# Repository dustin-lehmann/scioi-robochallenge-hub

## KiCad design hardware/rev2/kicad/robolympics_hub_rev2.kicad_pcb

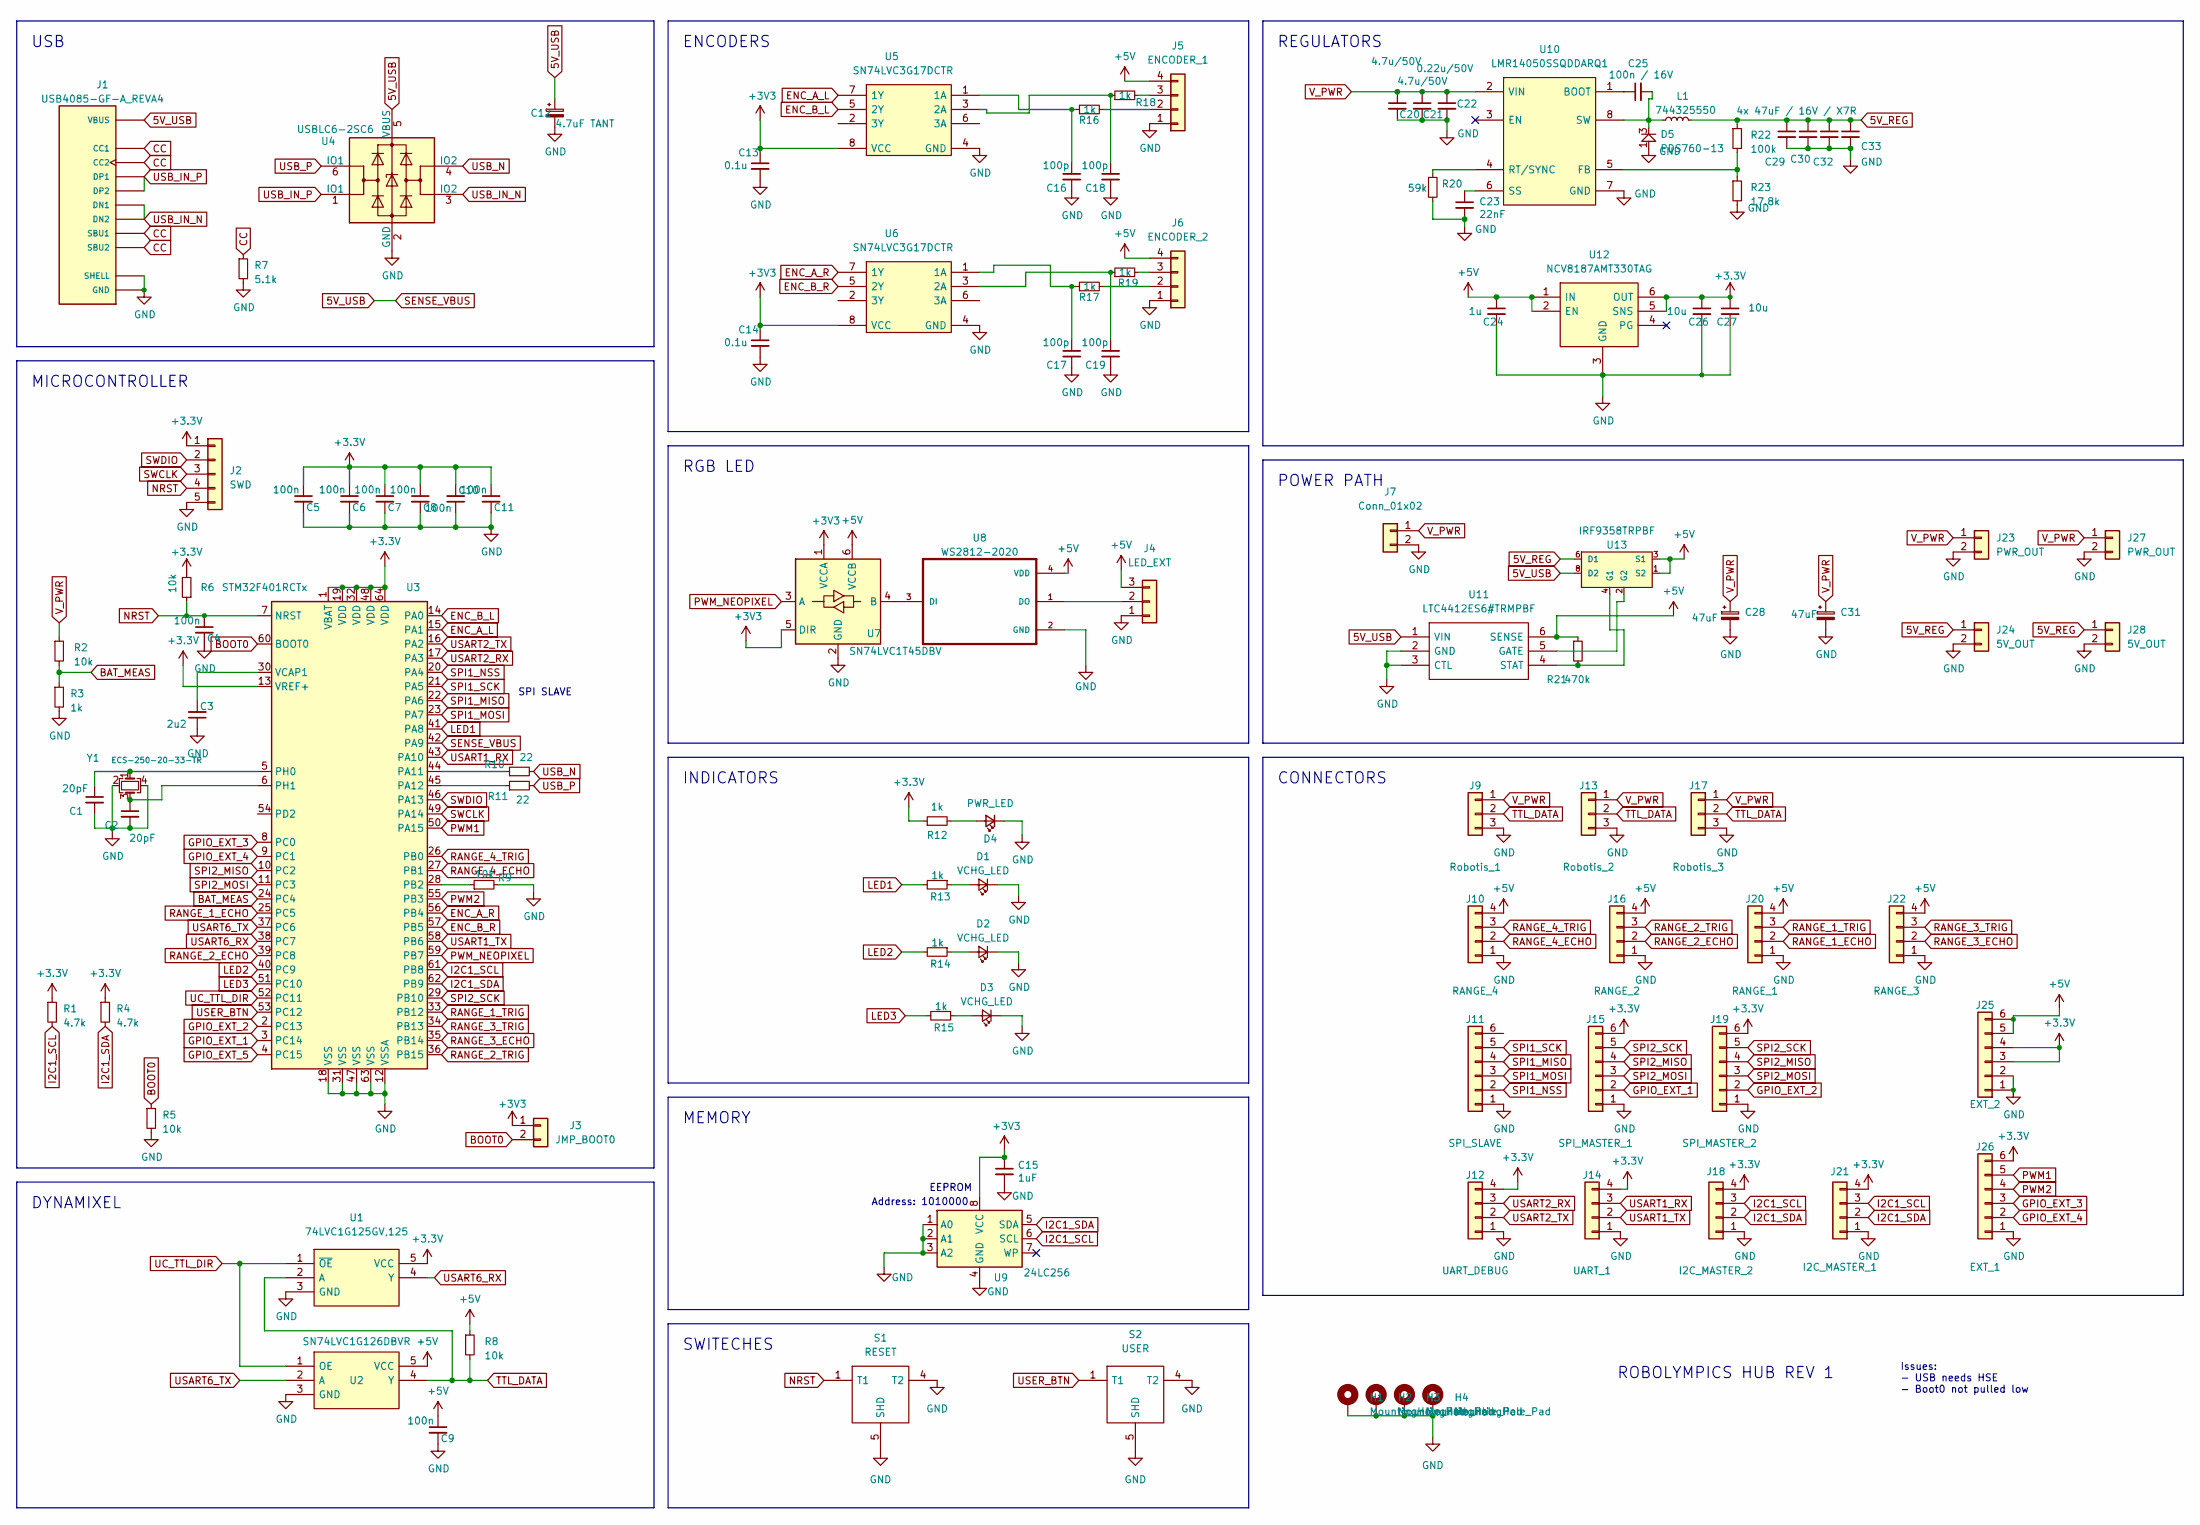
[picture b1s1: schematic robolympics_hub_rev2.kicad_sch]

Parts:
C1, C2: 20pF; C_0603_1608Metric
C3: 2u2; C_0805_2012Metric
C4, C5, C6, C7, C8, C9, C10, C11: 100n; C_0603_1608Metric
C12: 4.7uF TANT; C_1206_3216Metric
C13, C14: 0.1u; C_0603_1608Metric
C15: 1uF; C_0805_2012Metric
C16, C17, C18, C19: 100p; C_0603_1608Metric
C20, C21: 4.7u/50V; C_1210_3225Metric
C22: 0.22u/50V; C_0805_2012Metric
C23: 22nF; C_0603_1608Metric
C24: 1u; C_0805_2012Metric
C25: 100n / 16V; C_0603_1608Metric
C26, C27: 10u; C_0805_2012Metric
C28, C31: 47uF; CP_Elec_6.3x5.2
C29: 4x 47uF / 16V / X7R; C_1210_3225Metric
C30, C32, C33: C_Small; C_1210_3225Metric
D1, D2, D3: VCHG_LED; LED_0402_1005Metric
D4: PWR_LED; LED_0603_1608Metric
D5: PDS760-13; POWERDI5; Mouser Part Number 621-PDS760-F
H1, H2, H3, H4: MountingHole_Pad; MountingHole_2.7mm_M2.5_Pad
J1: USB4085-GF-A_REVA4; GCT_USB4085-GF-A_REVA4; PARTREV A4
J2: SWD; PinHeader_1x05_P2.54mm_Vertical
J3: JMP_BOOT0; PinHeader_1x02_P2.54mm_Vertical
J4: LED_EXT; Molex_KK-254_AE-6410-03A_1x03_P2.54mm_Vertical
J5: ENCODER_1; Molex_KK-254_AE-6410-04A_1x04_P2.54mm_Vertical
J6: ENCODER_2; Molex_KK-254_AE-6410-04A_1x04_P2.54mm_Vertical
J7: Conn_01x02; 691322310002
J9: Robotis_1; JST_EH_B3B-EH-A_1x03_P2.50mm_Vertical
J10: RANGE_4; Molex_KK-254_AE-6410-04A_1x04_P2.54mm_Vertical
J11: SPI_SLAVE; Molex_KK-254_AE-6410-06A_1x06_P2.54mm_Vertical
J12: UART_DEBUG; Molex_KK-254_AE-6410-04A_1x04_P2.54mm_Vertical
J13: Robotis_2; JST_EH_B3B-EH-A_1x03_P2.50mm_Vertical
J14: UART_1; Molex_KK-254_AE-6410-04A_1x04_P2.54mm_Vertical
J15: SPI_MASTER_1; Molex_KK-254_AE-6410-06A_1x06_P2.54mm_Vertical
J16: RANGE_2; Molex_KK-254_AE-6410-04A_1x04_P2.54mm_Vertical
J17: Robotis_3; JST_EH_B3B-EH-A_1x03_P2.50mm_Vertical
J18: I2C_MASTER_2; Molex_KK-254_AE-6410-04A_1x04_P2.54mm_Vertical
J19: SPI_MASTER_2; Molex_KK-254_AE-6410-06A_1x06_P2.54mm_Vertical
J20: RANGE_1; Molex_KK-254_AE-6410-04A_1x04_P2.54mm_Vertical
J21: I2C_MASTER_1; Molex_KK-254_AE-6410-04A_1x04_P2.54mm_Vertical
J22: RANGE_3; Molex_KK-254_AE-6410-04A_1x04_P2.54mm_Vertical
J23, J27: PWR_OUT; Molex_KK-254_AE-6410-02A_1x02_P2.54mm_Vertical
J24, J28: 5V_OUT; Molex_KK-254_AE-6410-02A_1x02_P2.54mm_Vertical
J25: EXT_2; Molex_KK-254_AE-6410-06A_1x06_P2.54mm_Vertical
J26: EXT_1; Molex_KK-254_AE-6410-06A_1x06_P2.54mm_Vertical
L1: 744325550; INDPM105102X500N
R1, R4: 4.7k; R_0603_1608Metric
R2, R5, R6, R8, R9: 10k; R_0603_1608Metric
R3, R12, R13, R14, R15, R16, R17, R18, R19: 1k; R_0603_1608Metric
R7: 5.1k; R_0603_1608Metric
R10, R11: 22; R_0603_1608Metric
R20: 59k; R_0603_1608Metric
R21: 470k; R_0603_1608Metric
R22: 100k; R_0603_1608Metric
R23: 17.8k; R_0603_1608Metric
S1: RESET; TL6330AF200Q; Mouser Part Number 612-TL6330AF200Q
S2: USER; TL6330AF200Q; Mouser Part Number 612-TL6330AF200Q
U1: 74LVC1G125GV,125; SOT95P275X110-5N; Mouser Part Number 771-74LVC1G125GV
U2: SN74LVC1G126DBVR; SOT95P275X110-5N; Mouser Part Number 595-SN74LVC1G126DBVR
U3: STM32F401RCTx; LQFP-64_10x10mm_P0.5mm
U4: USBLC6-2SC6; SOT-23-6
U5, U6: SN74LVC3G17DCTR; SOP65P400X130-8N; Mouser Part Number 595-SN74LVC3G17DCTR
U7: SN74LVC1T45DBV; SOT-23-6
U8: WS2812-2020; ws2812_2020
U9: 24LC256; DFN-8-1EP_6x5mm_P1.27mm_EP2x2mm
U10: LMR14050SSQDDARQ1; SOIC127P600X170-9N; Mouser Part Number 595-LMR14050SSDDARQ1
U11: LTC4412ES6#TRMPBF; SOT95P280X100-6N; Mouser Part Number 584-LTC4412ES6TRMPBF
U12: NCV8187AMT330TAG; SON65P200X200X80-7N; Mouser Part Number 863-NCV8187AMT120TAG
U13: IRF9358TRPBF; SOIC127P600X175-8N; MPN IRF9358TRPBF
Y1: ‎ECS-250-20-33-TR‎; ECS2501833BCKYTR

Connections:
5V_REG: C29.1, C30.1, C32.1, C33.1, J24.1, J28.1, L1.2, R22.1, U13.5 (D1_2), U13.6 (D1)
5V_USB: C12.1, J1.A4 (VBUS), J1.A9 (VBUS), J1.B4 (VBUS), J1.B9 (VBUS), U3.42 (PA9), U4.5 (VBUS), U11.1 (VIN), U13.7 (D2_2), U13.8 (D2)
+5V: C9.1, C24.1, J4.3, J5.4, J6.4, J10.4, J16.4, J20.4, J22.4, J25.5, J25.6, R8.1, R21.1, U2.5 (VCC), U7.6 (VCCB), U8.4 (VDD), U11.6 (SENSE), U12.1 (IN), U12.2 (EN), U13.1 (S2), U13.3 (S1)
BAT_MEAS: R2.2, R3.1, U3.24 (PC4)
BOOT0: J3.2, R5.1, U3.60 (BOOT0)
CC: J1.A5 (CC1), J1.A8 (SBU1), J1.B5 (CC2), J1.B8 (SBU2), R7.1
ENC_A_L: U3.15 (PA1), U5.7 (1Y)
ENC_A_R: U3.56 (PB4), U6.7 (1Y)
ENC_B_L: U3.14 (PA0), U5.5 (2Y)
ENC_B_R: U3.57 (PB5), U6.5 (2Y)
GND: C1.2, C2.2, C3.1, C4.2, C5.2, C6.2, C7.2, C8.2, C9.2, C10.1, C11.2, C12.2, C13.2, C14.2, C15.2, C16.2, C17.2, C18.2, C19.2, C20.2, C21.2, C22.2, C23.2, C24.2, C26.2, C27.2, C28.2, C29.2, C30.2, C31.2, C32.2, C33.2, D1.1 (K), D2.1 (K), D3.1 (K), D4.1 (K), D5.1, D5.2 (RIGHT_PIN), H1.1, H2.1, H3.1, H4.1, J1.A1 (GND), J1.A12 (GND), J1.B1 (GND), J1.B12 (GND), J1.P1 (SHELL), J1.P2 (SHELL), J1.P3 (SHELL), J1.P4 (SHELL), J2.5, J4.1, J5.1, J6.1, J7.2, J9.3, J10.1, J11.1, J12.1, J13.3, J14.1, J15.1, J16.1, J17.3, J18.1, J19.1, J20.1, J21.1, J22.1, J23.2, J24.2, J25.1, J25.2, J26.1, J27.2, J28.2, R3.2, R5.2, R7.2, R9.2, R20.2, R23.2, S1.3, S1.4 (T2), S1.5 (SHD), S2.3, S2.4 (T2), S2.5 (SHD), U1.3 (GND), U2.3 (GND), U3.12 (VSSA), U3.18 (VSS), U3.31 (VSS), U3.47 (VSS), U3.63 (VSS), U4.2 (GND), U5.4 (GND), U6.4 (GND), U7.2 (GND), U8.2 (GND), U9.1 (A0), U9.2 (A1), U9.3 (A2), U9.4 (GND), U10.7 (GND), U10.9 (GND_2), U11.2 (GND), U11.3 (CTL), U12.3 (GND), U12.7 (GND), Y1.2, Y1.4
GPIO_EXT_1: J15.2, U3.3 (PC14)
GPIO_EXT_2: J19.2, U3.2 (PC13)
GPIO_EXT_3: J26.3, U3.8 (PC0)
GPIO_EXT_4: J26.2, U3.9 (PC1)
GPIO_EXT_5: U3.4 (PC15)
I2C1_SCL: J18.3, J21.3, R1.2, U3.61 (PB8), U9.6 (SCL)
I2C1_SDA: J18.2, J21.2, R4.2, U3.62 (PB9), U9.5 (SDA)
LED1: R13.2, U3.41 (PA8)
LED2: R14.2, U3.40 (PC9)
LED3: R15.2, U3.51 (PC10)
NRST: C4.1, J2.4, R6.1, S1.1 (T1), S1.2, U3.7 (NRST)
unnamed: C1.1, U3.5 (PH0), Y1.1
unnamed: C2.1, U3.6 (PH1), Y1.3
unnamed: C3.2, U3.30 (VCAP1)
unnamed: C16.1, R16.1, U5.1 (1A)
unnamed: C17.1, R17.1, U6.1 (1A)
unnamed: C18.1, R18.1, U5.3 (2A)
unnamed: C19.1, R19.1, U6.3 (2A)
unnamed: C23.1, U10.6 (SS)
unnamed: C25.1, U10.1 (BOOT)
unnamed: C25.2, D5.3, L1.1, U10.8 (SW)
unnamed: D1.2 (A), R13.1
unnamed: D2.2 (A), R14.1
unnamed: D3.2 (A), R15.1
unnamed: D4.2 (A), R12.2
unnamed: J4.2, U8.1 (DO)
unnamed: J5.2, R16.2
unnamed: J5.3, R18.2
unnamed: J6.2, R17.2
unnamed: J6.3, R19.2
unnamed: R9.1, U3.28 (PB2)
unnamed: R10.1, U3.44 (PA11)
unnamed: R11.1, U3.45 (PA12)
unnamed: R20.1, U10.4 (RT/SYNC)
unnamed: R21.2, U11.4 (STAT), U13.4 (G1)
unnamed: R22.2, R23.1, U10.5 (FB)
unnamed: U7.4 (B), U8.3 (DI)
unnamed: U11.5 (GATE), U13.2 (G2)
PWM1: J26.5, U3.50 (PA15)
PWM2: J26.4, U3.55 (PB3)
PWM_NEOPIXEL: U3.59 (PB7), U7.3 (A)
RANGE_1_ECHO: J20.2, U3.25 (PC5)
RANGE_1_TRIG: J20.3, U3.33 (PB12)
RANGE_2_ECHO: J16.2, U3.39 (PC8)
RANGE_2_TRIG: J16.3, U3.36 (PB15)
RANGE_3_ECHO: J22.2, U3.35 (PB14)
RANGE_3_TRIG: J22.3, U3.34 (PB13)
RANGE_4_ECHO: J10.2, U3.27 (PB1)
RANGE_4_TRIG: J10.3, U3.26 (PB0)
SPI1_MISO: J11.4, U3.22 (PA6)
SPI1_MOSI: J11.3, U3.23 (PA7)
SPI1_NSS: J11.2, U3.20 (PA4)
SPI1_SCK: J11.5, U3.21 (PA5)
SPI2_MISO: J15.4, J19.4, U3.10 (PC2)
SPI2_MOSI: J15.3, J19.3, U3.11 (PC3)
SPI2_SCK: J15.5, J19.5, U3.29 (PB10)
SWCLK: J2.3, U3.49 (PA14)
SWDIO: J2.2, U3.46 (PA13)
TTL_DATA: J9.2, J13.2, J17.2, R8.2, U1.2 (A), U2.4 (Y)
UC_TTL_DIR: U1.1 (~OE), U2.1 (OE), U3.52 (PC11)
USART1_RX: J14.3, U3.43 (PA10)
USART1_TX: J14.2, U3.58 (PB6)
USART2_RX: J12.3, U3.17 (PA3)
USART2_TX: J12.2, U3.16 (PA2)
USART6_RX: U1.4 (Y), U3.38 (PC7)
USART6_TX: U2.2 (A), U3.37 (PC6)
USB_IN_N: J1.A7 (DN1), J1.B7 (DN2), U4.3 (IO2)
USB_IN_P: J1.A6 (DP1), J1.B6 (DP2), U4.1 (IO1)
USB_N: R10.2, U4.4 (IO2)
USB_P: R11.2, U4.6 (IO1)
USER_BTN: S2.1 (T1), S2.2, U3.53 (PC12)
V_PWR: C20.1, C21.1, C22.1, C28.1, C31.1, J7.1, J9.1, J13.1, J17.1, J23.1, J27.1, R2.1, U10.2 (VIN)

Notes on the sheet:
EEPROM
SWITECHES
REGULATORS
CONNECTORS
Issues: - USB needs HSE - Boot0 not pulled low
Address: 1010000
RGB LED
MICROCONTROLLER
MEMORY
POWER PATH
INDICATORS
ROBOLYMPICS HUB REV 1
DYNAMIXEL
USB
SPI SLAVE
ENCODERS

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
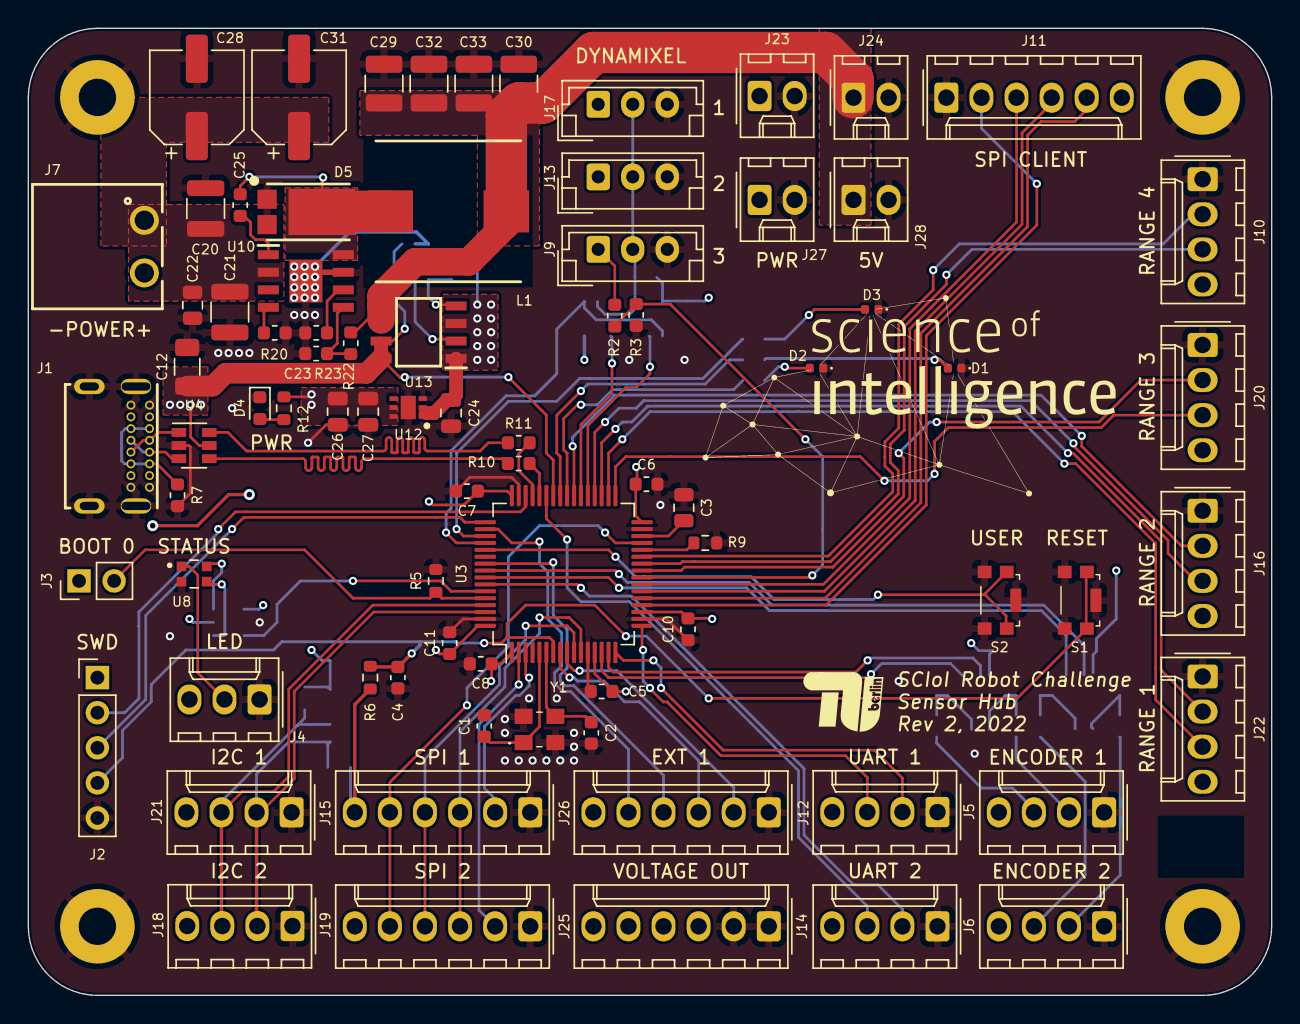
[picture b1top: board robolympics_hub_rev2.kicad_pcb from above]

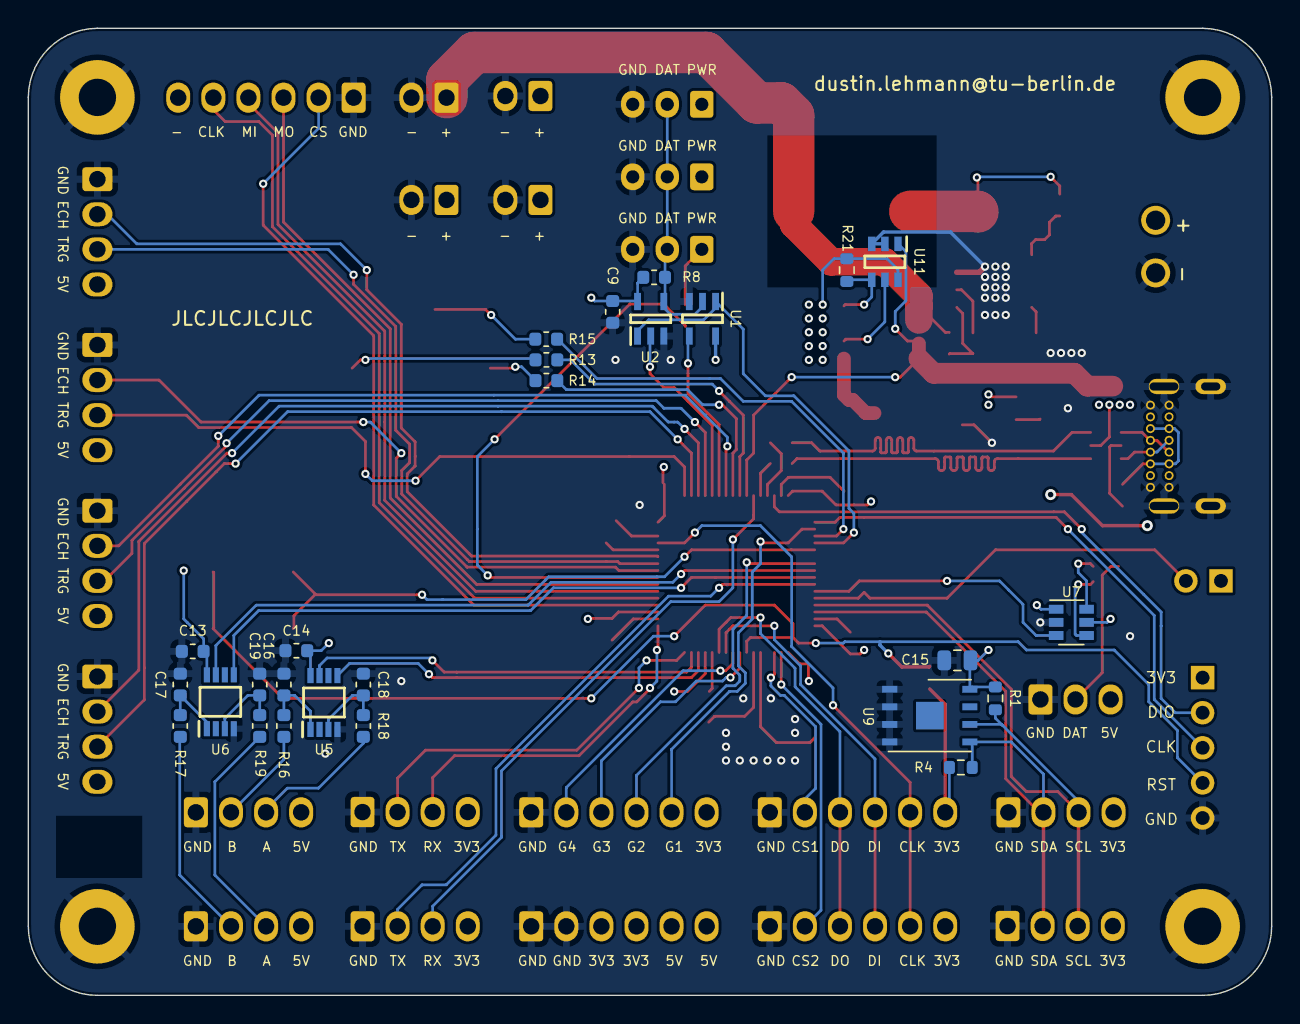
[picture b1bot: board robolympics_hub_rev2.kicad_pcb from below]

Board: 4 copper layers, 90.0 x 70.0 mm, 109 parts (26 on the bottom side), 83 nets.

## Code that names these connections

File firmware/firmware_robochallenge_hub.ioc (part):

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Mcu.Name=STM32F401R(B-C)Tx
Mcu.Package=LQFP64
Mcu.UserName=STM32F401RCTx
PA11.Mode=Device_Only
PA11.Signal=USB_OTG_FS_DM
PA12.Mode=Device_Only
PA12.Signal=USB_OTG_FS_DP
PA13.Mode=Serial_Wire
PA13.Signal=SYS_JTMS-SWDIO
PA14.Mode=Serial_Wire
PA14.Signal=SYS_JTCK-SWCLK
PA8.Signal=GPIO_Output
PB0.GPIOParameters=GPIO_Speed,GPIO_Label
PB0.GPIO_Label=RANGE_4_TRIG
PB0.GPIO_Speed=GPIO_SPEED_FREQ_MEDIUM
PB0.Signal=GPIO_Output
PB1.GPIOParameters=GPIO_PuPd,GPIO_Label,GPIO_ModeDefaultEXTI
PB1.GPIO_Label=RANGE_4_ECHO
PB1.GPIO_ModeDefaultEXTI=GPIO_MODE_IT_RISING_FALLING
PB1.GPIO_PuPd=GPIO_PULLDOWN
PB1.Signal=GPXTI1
PB13.GPIOParameters=GPIO_Speed,GPIO_Label
PB13.GPIO_Label=RANGE_3_TRIG
PB13.GPIO_Speed=GPIO_SPEED_FREQ_MEDIUM
PB13.Signal=GPIO_Output
PB14.GPIOParameters=GPIO_PuPd,GPIO_Label,GPIO_ModeDefaultEXTI
PB14.GPIO_Label=RANGE_3_ECHO
PB14.GPIO_ModeDefaultEXTI=GPIO_MODE_IT_RISING_FALLING
PB14.GPIO_PuPd=GPIO_PULLDOWN
PB14.Signal=GPXTI14
PB7.Signal=S_TIM4_CH2
PC10.Signal=GPIO_Output
PC9.Signal=GPIO_Output
RCC.HSE_VALUE=25000000
RCC.SYSCLKFreq_VALUE=48000000
RCC.SYSCLKSource=RCC_SYSCLKSOURCE_PLLCLK
board=custom

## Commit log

2022-03-09 - uploaded schematics for rev1
2022-03-15 - added distance sensors and streaming messages
2022-03-17 - bugfix for distance sensors
